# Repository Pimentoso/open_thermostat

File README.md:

# open_thermostat

A lightweight, open-source thermostat controller. Based on Lolin S2 mini board

## Quickstart

Install
```bash
git clone https://github.com/your-org/open_thermostat.git
cd open_thermostat
python -m venv .venv
source .venv/bin/activate
esphome run open_thermostat.yaml
```

## TODO

- Add 4.7k resistor on temp sensor
- Change button pin to GPIO1–6, GPIO14–18, GPIO21

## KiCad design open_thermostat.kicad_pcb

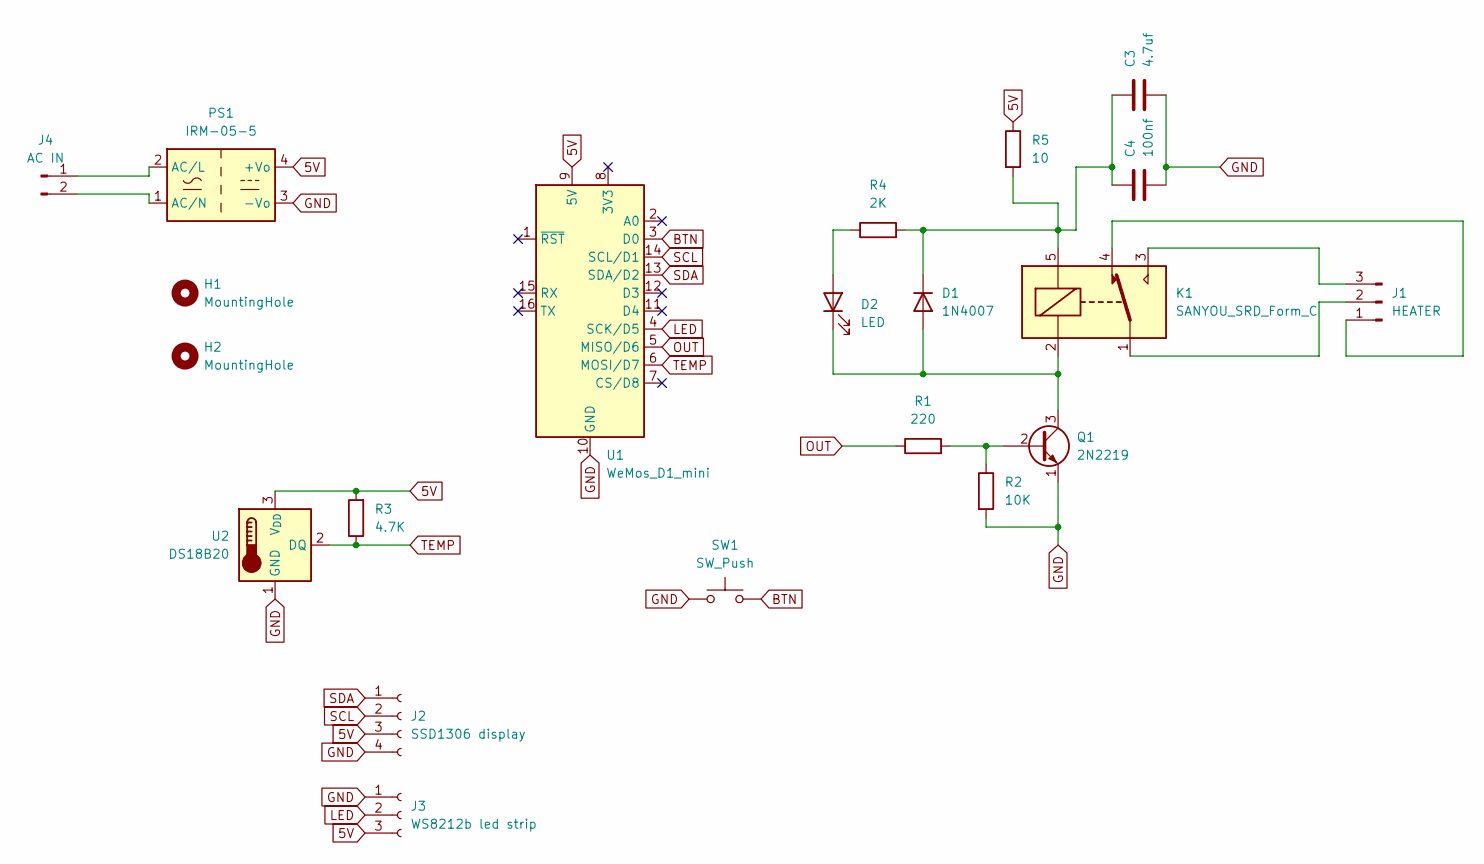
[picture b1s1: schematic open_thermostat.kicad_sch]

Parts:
C3: 4.7uf; C_1206_3216Metric_Pad1.33x1.80mm_HandSolder
C4: 100nf; C_1206_3216Metric_Pad1.33x1.80mm_HandSolder
D1: 1N4007; D_DO-41_SOD81_P10.16mm_Horizontal
D2: LED; LED_D5.0mm
H1, H2: MountingHole; MountingHole_4.3mm_M4
J1: HEATER; TerminalBlock_MetzConnect_Type094_RT03503HBLU_1x03_P5.00mm_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
J2: SSD1306 display; JST_XH_B4B-XH-A_1x04_P2.50mm_Vertical
J3: WS8212b led strip; JST_XH_B3B-XH-A_1x03_P2.50mm_Vertical
J4: AC IN; TerminalBlock_MetzConnect_Type094_RT03502HBLU_1x02_P5.00mm_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
K1: SANYOU_SRD_Form_C; Relay_SPDT_SANYOU_SRD_Series_Form_C
PS1: IRM-05-5; 220v AC to 5v DC Transformer
Q1: 2N2219; SOT-23_Handsoldering
R1: 220; R_1206_3216Metric_Pad1.30x1.75mm_HandSolder
R2: 10K; R_1206_3216Metric_Pad1.30x1.75mm_HandSolder
R3: 4.7K; R_1206_3216Metric_Pad1.30x1.75mm_HandSolder
R4: 2K; R_1206_3216Metric_Pad1.30x1.75mm_HandSolder
R5: 10; R_1206_3216Metric_Pad1.30x1.75mm_HandSolder
SW1: SW_Push; SW_Push_1P1T_NO_6x6mm_H9.5mm
U1: WeMos_D1_mini; WEMOS_D1_mini_light
U2: DS18B20; TO-92_Inline

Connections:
5V: J2.3, J3.3, PS1.4 (+Vo), R3.2, R5.1, U1.9 (5V), U2.3 (V_{DD})
BTN: SW1.2, U1.3 (D0)
GND: C3.1, C4.1, J2.4, J3.1, PS1.3 (-Vo), Q1.1 (E), R2.2, SW1.1, U1.10 (GND), U2.1 (GND)
LED: J3.2, U1.4 (SCK/D5)
unnamed: D1.2 (A), D2.1 (K), K1.2, Q1.3 (C)
unnamed: C3.2, C4.2, D1.1 (K), K1.5, R4.2, R5.2
unnamed: D2.2 (A), R4.1
unnamed: J1.1, K1.4
unnamed: J1.2, K1.1
unnamed: J1.3, K1.3
unnamed: J4.1, PS1.2 (AC/L)
unnamed: J4.2, PS1.1 (AC/N)
unnamed: Q1.2 (B), R1.2, R2.1
OUT: R1.1, U1.5 (MISO/D6)
SCL: J2.2, U1.14 (SCL/D1)
SDA: J2.1, U1.13 (SDA/D2)
TEMP: R3.1, U1.6 (MOSI/D7), U2.2 (DQ)

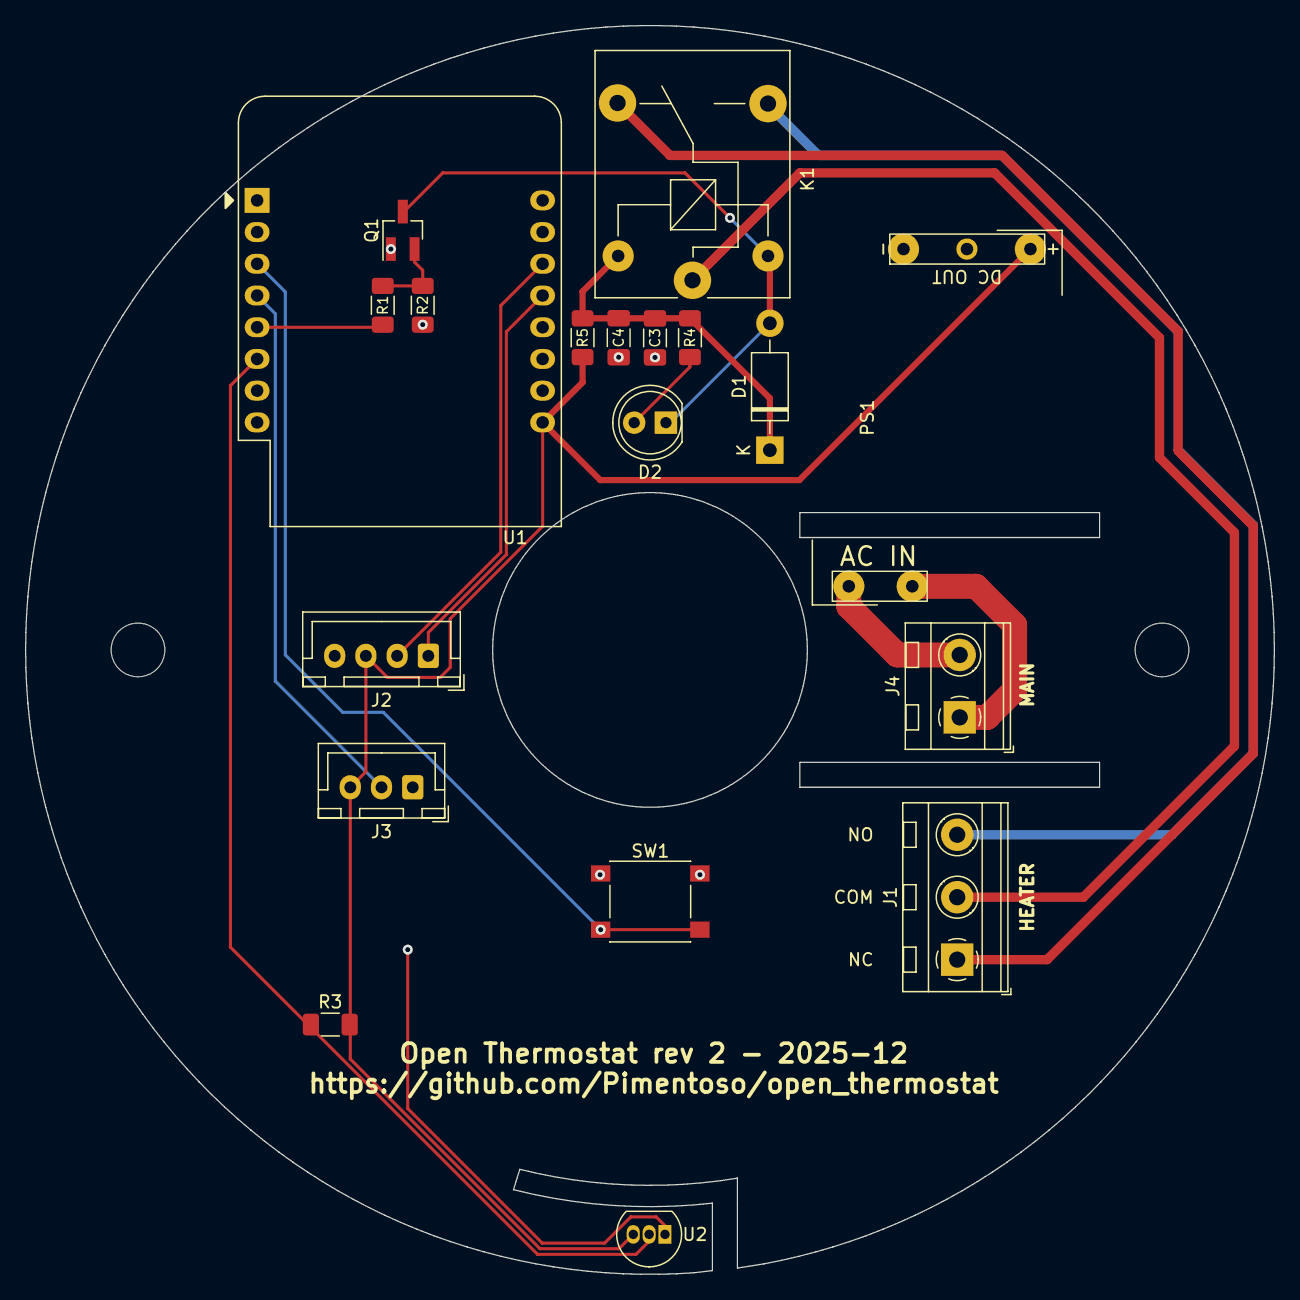
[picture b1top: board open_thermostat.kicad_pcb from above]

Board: 2 copper layers, 100.0 x 100.0 mm, 21 parts (0 on the bottom side), 17 nets.

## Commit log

2025-12-17 esphome yaml file
2025-12-23 pcb fixes
2025-12-23 gitignore
2025-12-23 yaml fixes
2025-12-26 edit light effect
2025-12-26 add light turn on delay to avoid boot loop
    weird issue about the board failing to boot when the lights were on during reset. It tried to power them on when the component was not fully ready. Log:
    Guru Meditation Error: Core 0 panic'ed (LoadProhibited). Exception was unhandled.
    WARNING Decoded 0x4011bfa7: esphome::light::LightState::get_output() const at /Users/miche/Documents/Github/open_thermostat/esphome/.esphome/build/open-thermostat/src/esphome/components/light/light_s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
2025-12-31 add status led and fix temp values
2025-12-31 add readme stub
2025-12-31 more fixes
2026-02-27 wip new version
